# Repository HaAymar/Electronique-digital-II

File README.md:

# Electronique-digital-II

## Projet d'éléctronique digital 

### Groupe J
### Membres du groupe
* BLERVAQUE Thomas
* HAKIZIMANA Aymar Davy
* HURT Victor
* KOUVAHE Folly Serge
* PARMENTIER Charles

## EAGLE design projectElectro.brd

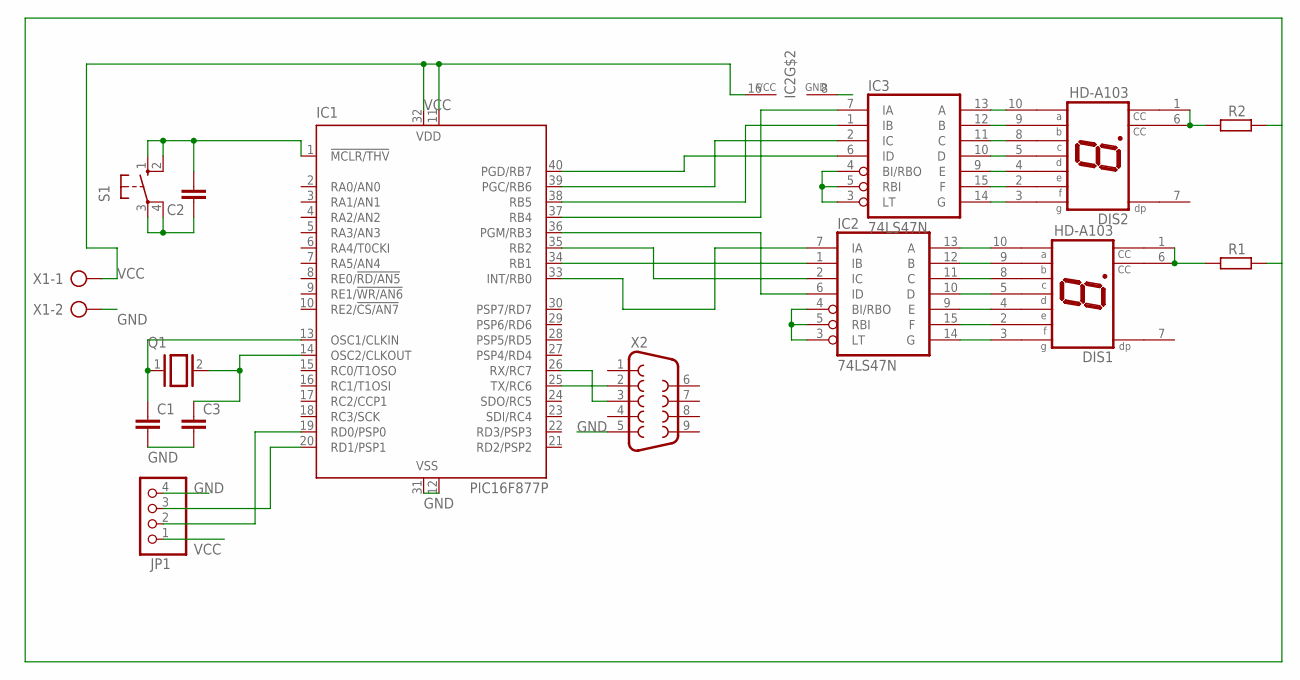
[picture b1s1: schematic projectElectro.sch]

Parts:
C1, C2, C3: C-EU025-025X050; C025-025X050
DIS1, DIS2: HD-A103; HDSP-A
IC1: PIC16F877P; DIL40
IC2, IC3: 74LS47N; DIL16
JP1: PINHD-1X4; 1X04
Q1: XTAL/S; QS
R1, R2: R-EU_0207/10; 0207/10
S1: 10-XX; B3F-10XX
X1: AK300/2
X2: F09H

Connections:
GND: C1.2, C3.2, IC1.12 (VSS), IC1.31 (VSS), IC3.8 (GND), JP1.4, X1.2, X2.5
unnamed: IC1.25 (TX/RC6), X2.2
unnamed: IC1.26 (RX/RC7), X2.3
unnamed: IC1.36 (PGM/RB3), IC2.6 (ID)
unnamed: IC2.3 (LT), IC2.4 (BI/RBO), IC2.5 (RBI)
unnamed: IC1.35 (RB2), IC2.2 (IC)
unnamed: IC1.34 (RB1), IC2.1 (IB)
unnamed: IC1.33 (INT/RB0), IC2.7 (IA)
unnamed: DIS1.10 (A), IC2.13 (A)
unnamed: DIS1.9 (B), IC2.12 (B)
unnamed: DIS1.8 (C), IC2.11 (C)
unnamed: DIS1.5 (D), IC2.10 (D)
unnamed: DIS1.4 (E), IC2.9 (E)
unnamed: DIS1.2 (F), IC2.15 (F)
unnamed: DIS1.3 (G), IC2.14 (G)
unnamed: DIS1.1 (CC), DIS1.6 (CC), R1.1
unnamed: IC3.3 (LT), IC3.4 (BI/RBO), IC3.5 (RBI)
unnamed: IC1.37 (RB4), IC3.7 (IA)
unnamed: C2.2, IC1.1 (!MCLR/THV), S1.1 (S), S1.2 (S1)
unnamed: C2.1, S1.3, S1.4 (P1)
unnamed: C1.1, IC1.13 (OSC1/CLKIN), Q1.1
unnamed: C3.1, IC1.14 (OSC2/CLKOUT), Q1.2
unnamed: IC1.38 (RB5), IC3.1 (IB)
unnamed: DIS2.10 (A), IC3.13 (A)
unnamed: IC1.19 (RD0/PSP0), JP1.2
unnamed: IC1.39 (PGC/RB6), IC3.2 (IC)
unnamed: IC1.20 (RD1/PSP1), JP1.3
unnamed: IC1.40 (PGD/RB7), IC3.6 (ID)
unnamed: DIS2.9 (B), IC3.12 (B)
unnamed: DIS2.8 (C), IC3.11 (C)
unnamed: DIS2.5 (D), IC3.10 (D)
unnamed: DIS2.4 (E), IC3.9 (E)
unnamed: DIS2.2 (F), IC3.15 (F)
unnamed: DIS2.3 (G), IC3.14 (G)
unnamed: DIS2.1 (CC), DIS2.6 (CC), R2.1
VCC: IC1.11 (VDD), IC1.32 (VDD), IC2.16 (VCC), IC3.16 (VCC), JP1.1, X1.1

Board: 2 copper layers, 15 parts (0 on the bottom side), 36 nets, no tracks yet.

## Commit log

2022-05-16 [ADD]Additing of a report of the project
2022-05-17 [Update]Update of code C
2022-05-17 [UPDATE]Update of code in C
